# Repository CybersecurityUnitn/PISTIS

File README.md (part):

# PISTIS
### Trusted Computing Architecture for Low-end Embedded Systems 
This repository includes all of the source files and helper scripts for **PISTIS**, a Trusted Execution Environment documented in the scientific paper "*PISTIS: Trusted Computing Architecture for Low-end Embedded Systems*" by Michele Grisafi, Mahmoud Ammar, Marco Roveri and Bruno Crispo. The article, presented at the USENIX Security '22 conference, discloses the content of this repository as an open source contribution to the scientific community.

If you have any questions on the content of the repository, feel free to contact the main author at michele.grisafi@unitn.it.

We highly recommend reading the scientific article before diving into this report!

Following, there is a list of instructions and broad guidelines on how to compile, run and test PISTIS. Depending on the board used for this evaluation, on the programming environment and the tools used, the behaviour of this implementation might change. 

**Disclaimer**: *The following is a working proof of concept. There might be bugs and inconsistencies which were not addressed. Furthermore, the code might damage your MCU board, erasing its memory or degrading its hardware. Use it at your own risk, we do not assume any responsibility for the use of this code, or for the damage it can cause.*

## Table of Content
- [PISTIS](#pistis)
   * [Content of this repository](#content-of-this-repository)
- [Introduction](#introduction)
   * [Isolation details](#isolation-details)
      + [Interrupts](#interrupts)
   * [Memory Map](#memory-map)
- [Running PISTIS](#running-pistis)
   * [Pre requisites](#pre-requisites)
   * [Loading PISTIS TCM (with the default untrusted application)](#loading-pistis-tcm-with-the-default-untrusted-application)
   * [Applications updates / Remote deployments](#applications-updates--remote-deployments)
      + [Compiling the update/application ](#compiling-the-updateapplication)
      + [Deploying untrusted update](#deploying-untrusted-update)
   * [LED signals](#led-signals)
   * [(optional) Loading the custom BSL](#optional-loading-the-custom-bsl)
      + [(optional) Loading the key](#optional-loading-the-key)
   * [Library instrumentation](#library-instrumentation)
      + [Optimisations](#optimisations)
      + [Debug and measurements](#debug-and-measurements)
- [APIs Description](#apis-description)
   * [Data Types](#data-types)
   * [Constants](#constants)
   * [Trusted Application APIs](#trusted-application-apis)
      + [Secure Remote Update](#secure-remote-update)
         - [**callReceiveUpdate**](#callreceiveupdate)
      + [Remote Attestation ](#remote-attestation)
         - [**callAttestCode**](#callattestcode)
   * [Private TCM APIs](#private-tcm-apis)
      + [Functions endpoints](#functions-endpoints)
         - [**launchAppCode**](#launchappcode)
         - [**verify_app_inst**](#verify_app_inst)
         - [**verify_app_cfi**](#verify_app_cfi)
         - [**isImmediateSafeValue**](#isimmediatesafevalue)
         - [**getSecureKey**](#getsecurekey)
         - [**setSecureKey**](#setsecurekey)
   * [Public TCM APIs](#public-tcm-apis)
      + [Assembly endpoints](#assembly-endpoints)
         - [**safe_br_fun**](#safe_br_fun)
         - [**safe_bra_fun**](#safe_bra_fun)
         - [**safe_call_fun**](#safe_call_fun)
         - [**safe_calla_fun**](#safe_calla_fun)
         - [**safe_ret_fun**](#safe_ret_fun)
         - [**safe_reta_fun**](#safe_reta_fun)
         - [**safe_reti_fun**](#safe_reti_fun)
         - [**write_mov_fun**](#write_mov_fun)
         - [**write_movx_fun**](#write_movx_fun)
         - [**write_xor_fun**](#write_xor_fun)
         - [**write_xorx_fun**](#write_xorx_fun)
         - [**write_add_fun**](#write_add_fun)
         - [**write_addx_fun**](#write_addx_fun)
         - [**write_addc_fun**](#write_addc_fun)
         - [**write_addcx_fun**](#write_addcx_fun)
         - [**write_dadd_fun**](#write_dadd_fun)
         - [**write_daddx_fun**](#write_daddx_fun)
         - [**write_sub_fun**](#write_sub_fun)
         - [**write_subx_fun**](#write_subx_fun)
         - [**write_subc_fun**](#write_subc_fun)
         - [**write_subcx_fun**](#write_subcx_fun)

## Content of this repository
- `BSL/`: this folder contains the files required for the modification of the BSL.
    - `IAR_BSL_Source/`: folder containing the IAR Workbench BSL project, used for flashing the new BSL into the device.
    - `modifiedFiles/`: folder containing the modified files used for PISTIS custom BSL.
        - `BSL430_Command_Interpreter.c`: file containing the command interpreter code, used to parse the BSL commands received. We are removing some of the functionalities of the BSL from this file to make room for our PISTIS Secure Storage.
        - `BSL430_Low_Level_Init.s43`: BSL interface for the program, containing the Z-area. We added some entries to this area, such as the BSL unlock function. This will be called by the TCM to enable write privileges over the BSL.
        - `lnk_msp430f5438a.ld`: BSL linker file.
    - `loadKey.c`: source file to load a custom cryptographic key onto PISTIS Safe Storage.
- `UpdateApplication/`: this folder contains all of the required files for compiling a single application for PISTIS. Specifically, it should be populated with the source files of the application.
    - `Makefile`: makefile for compiling the application to be deployed. The result is a file `deployable.out` which is ready for deployment.
    - `src/`: this folder should contain all of the source files of the user application to be compiled (both '.c' and '.s' files). 
- `TCM/`: this folder contains the source code of PISTIS TCM. Morevoer, it contains the source files of a user application (untrusted) that can be deployed alongside it without going over remote update.
    - `Makefile`: makefile for compiling both the untrusted application and the core of TCM. The result is the file `deployable.out` which is ready to be deployed on the MCU.
    - `app/`: folder containing all of the files required for the compilation of the untrusted application
        - `src/`: folder containing all of the source files, both '.c' and '.s' of the untrusted application
        - `Makefile.include`: makefile to be included, containing some directives for the compilation of the application by the main Makefile
    - `core/`: folder containing all of the files required for the PISTIS compilation.
        - `src/`: folder containing all of the source files, both '.c' and '.s' of PISTIS.
            - `core.c|.h`: file containing the source code for the main PISTIS functions.
            - `virt_fun.s`: assembly file containing the definitions of the various virtual functions.
            - `protected_isr.s`: assembly file containing the protected Interrupt Service Routines for the secure interrupt management.
            - `secureContextSwitch.c|.h`: source files for the secure context switch operations which allow the backup and restoration of the RAM, or any other hook operation during a safe context switch.
            - `TCMhook.h`: header file needed by the application (needs to be included in the source files with the '#include' directive) in order to call the secure update function. This file get automatically copied to the `app/src/` directory of the application.
        - `ext_modules/`: folder containing the source files of the various extensions. These files are copied in the `core/src/` folder by the makefile if specified.
            - `secureUpdate.c|.h`: source file for the secure update over serial communication.
            - `raHelper.c|.h`: source files for some backup/restore operations performed by the Remote Attestation.
            - `raHelperAsm.s`: assembly files for some backup/restore opearation performed by the Remote Attestation.
            - `remote_attestation/`: folder containing the HACL implementation of remote attestation.
                - `ra.c`: our implementation, leveraging the HACL library, of the remote attestation.
        
        - `Makefile.include`: makefile to be included, containing some directives for the compilation of the TCM by the main Makefile
- `toolchain/`: folder containing all of the scripts required by the makefile and the deployment process
    - `linkerScript.ld`: modified linker scripts containing the directives for the linker when compiling ONLY the application. Used exclusively by the Makefile.
    - `linkerScriptWithCore.ld`: modified linker scripts containing the directives for the linker when compiling both the application and the TCM. Used exclusively by the Makefile.
    - `loadProgram.py`: python script used to load the program onto the MCU via UART interface (serial port), in compliance with the PISTIS secure update protocol.
    - `metadata.py`: python script in charge of adding the required metadata to the output file. Used exclusively by the Makefile.
    - `modifier.py`: python script in charge of replacing unsafe instructions. Used exclusively by the Makefile.
    - `postprocessor.py`: python script in charge of rejecting the application in case of unsafe instructions (compile-time). Used exclusively by Makefile.
    - `gccLibraries/`: contains all of the statically linked libraries used by GCC and adapted to our toolchain (insertion of NOP slides and reserved registers). The `*.small` files inside refer to libraries using ret and call instead of reta and calla.
        - `libcrt.a`: statically linked library of gcc, compiled from the gcc source folder with the instrumented file `newlib/libgloss/msp430/crt0.S|crt_bss.S` which generates the compiled file `msp430-elf/large/full-memory-range/libgloss/msp430/libcrt.a`. The new file must be placed in `compilerGCCRoot/msp430-elf/lib/large/full-memory-range`. **crt0_movedata** and **crt0_init_bss** have been instrumented (adding the NOP slides). Others, such as call_main and call_exit are not but we should not need them.
        - `libgcc.a`: statically linked library compiled with a modified makefile (to prevent use of reserved registers '*-ffixed-r4 -ffixed-r5 -ffixed-r6*') `sourceGCC/gcc/libgcc/Makefile.in` yielding the file `build/gcc/msp430-elf/large/full-memory-range/libgcc/libgcc.a` to be placed in `compilerGCCRoot/lib/gcc/msp430-elf/9.2.0/large/full-memory-range`
        - `libnosys.a` and `libsim.a`: statically compiled files obtained from the modified makefile (to prevent use of reserved registers '*-ffixed-r4 -ffixed-r5 -ffixed-r6*') `sourceGCC/newlib/libgloss/msp430/Makefile.ini` yielding the files `build/gcc/msp430-elf/large/full-range-memory/libgloss/msp430/libnosys.a|libsim.a`. To be placed in `compiler//msp430-elf/lib/large/full-memory-range`
        - `libc.a`: statically linked library compiled with a modified makefiles (to prevent use of reserved registers '*-ffixed-r4 -ffixed-r5 -ffixed-r6*') `sourceGCC/newlib/newlib/libc/string/Makefile.in`,`sourceGCC/newlib/newlib/libc/string/Makefile.in`,`sourceGCC/newlib/newlib/libc/string/Makefile.in`  yielding the file `build/gcc/msp430-elf/large/full-memopry-range/newlib/libc.a`. 
        The new file must be placed in `compiler/msp430-elf/lib/large/full-memory-range`
    - `helperScripts/`: contains all of the scripts that are helpful in the creation of a proper application image
        - `auxGccPaser.py`: python script that parses a portion of mspdump code and performs the following operations:
            - Format the files to assembly standard.
            - Locates the relevant functions and labels, renaming them so that they can be compiled.
            - Replaces all of the jumps offsets, branches arguments and calla destinations with the correct label so that they can be relocated.
        - `getSizeData.py`: compiles every single test application and retrieves the size info of the various files.
        - `objToHex.py`: python script that parses an object file - created by the `metadata.py` script with the 'debugFiles' set to true - and outputs its content byte by byte so that it can be used in an `injectData.c` source file.
        - `runTimeEvaluation.c`: small C file containing the code used for the runTime evaluation. 
        - `powerConsumption/`: contains all of the scripts for getting the battery consumption with its graphs.
            - `Battery.java`: simulates the battery consumption at various execution rates.
            - `getConsumptions.sh`: script to get all of the power measures via the java script.
            - `getGraph.py`: script to generate graphs for the power measures obtained with the above script.
        - `remote_attestation/verifier/verifier.py`: python script acting simulating a verifier for the Remote Attestation. This script computes the HMAC of a block of data.     
    - `compiler/`: contains the various compilers used by PISTIS, with some compilation libraries and some backups.
        - `include_gcc/`: contains some of the includes files required by the compiler and provided by TI.
        - `msp430-gcc-9.2.0.50_linux64/`: contains the compiled GCC compiler used by PISTIS.
        - `msp430-gcc-9.2.0.50_linux64_backup/`: contains the backup of some of the files modified by our toolchain. These are required for the compilation of uninstrumented applications.
        - `msp430-gcc-9.2.0.50-source-full.tar.gz`: archive containing the modified source files (as described in the `gccLibraries/` folder) for the compilation of the desired libraries and executables.
- `TestApps/`: folder containing all of the test applications used during the evaluation of the proposed PISTIS implementation.
    - `ar-full/`: instrumented and correctly working
    - `bitcount/`: instrumented and correctly working
    - `SHA-256/`: instrumented and correctly working
    - `CopyCodeDMA/`: instrumented and correctly working. The Application copies the content of the flash into RAM with memcpy and with the DMA. In both cases, it checks whether the result is correct. The DMA triggers an interrupt when finished.
    - `CantorSet/`: instrumented and correctly working
    - `PolynomialAddiction/`: instrumented and correctly working
    - `CryptoCode/`: instrumented and correctly working
    - `Serial/`: instrumented and correctly working
    - `CartesianToPolar/`: instrumented and correctly working
    - `LargeSubsequence/`: instrumented and correctly working
    - `PrimeFactorisation/`: instrumented and correctly working
    - `SudokuSolver/`: LINKER problem
    - `TiBenchmark/`: folder containing all of the benchmark applications used by TI and during the evalution of the proposed PISTIS implementation.
        - `whet/`: instrumented and correctly working.
        - `matrixMultiplication/`: instrumented and correctly working.
        - `floatingPointMath/`: instrumented and correctly working.
        - `firFilter/`: instrumented and correctly working.
        - `dhry/`: instrumented and correctly working. NOT WORKING IN CCS
        - `8bitSwitchCase/`: instrumented and correctly working.
        - `16bitSwitchCase/`: instrumented and correctly working.
        - `8bitMath/`: instrumented and correctly working.
        - `16bitMath/`: instrumented and correctly working.
        - `32bitMath/`: instrumented and correctly working.
        - `8bit2dimMatrix/`: instrumented and correctly working.
        - `16bit2dimMatrix/`: instrumented and correctly working.

# Introduction
Pistis is a bare-metal Trusted Execution Environment (TEE) for low-end embedded systems with no support to MMU/MPU. As a TEE, Pistis creates a new execution environments where secure software can run without interference from the untrusted software. We refer to these two environments as the TEE and the Unstrusted Environment (UE). These two environments coexist on the device and are separated by Pistis' software-based primitives, which ensure that the TEE is completely isolated from the UE. 
Being a software-based TEE, Pistis relies on a Trusted Computing Module (TCM) to enforce the isolation between the two environments. The TCM is a piece of software acting as Root of Trust (RoT) that is run in the TEE, alongside other Trusted Applications (TAs). 
These TAs can be deployed by security developers to implement some arbitrary security services. These services can then be leveraged by any software running on the UE using a set of registered APIs. 

## Isolation details
The TCM enforces a software-based separation on the memory and the pheripherals of the device. Similarly to a TrustZone-enabled environment, the TEE has complete control over the entire device, while the UE has only *limited* control over the UE-assigned resources. At boot, the control is given to the TEE, where the TCM performs an initialisation of the device and of the UE environment, afterwhich the control is given to the UE. From that moment onward, there is a master-slave relationship between the TEE and the UE, with the former that is executed only upon request of the UE. 
The UE supports up to one single application binary, which must include the so called Untrusted Application. This application must comply with the Pistis' security policy, which is enforced by the TCM. For instance, the UE is not allowed to access any resource outside of the ones assigned to it by the TCM. Any violation of these policy will be detected at deployment time or at run time, and it trigger a device reset.
Pistis offers a custom toolchain to the UE developers that transparently makes the application binary compliant with Pistis security policy.

### Interrupts
Interrupts are not shared among the UE and the TEE. Conceptually, the TEE has full control over the interrupts, and allows the UE to register its own interrupt handlers. When an interrupt is triggered, the TEE will look up the interrupt table and invoke the right handler. This handler will then be executed in the TEE, which will then return the control to the UE. It is up to the TEE to decide whether to allow the UE to register a handler for a given interrupt or not.

## Memory Map
The software-based isolation of Flash, RAM and MMIO is achieved by means of a custom memory map. The memory map is defined in the linker script and is shown in the following table.

|Address|Name|Description|
|------|-----|-----------|
|0x000-fff|MMIO|Registers for pheripherals|
|0x1000-17ff|BSL/TEE Safe Storage| BSL and PISTIS Secure Storage|
|0x1800-19ff|Information Memory|Hardware info used for calibration of the board|
|0x1c00-2aff|TEE Ram|Ram used by PISTIS Trusted Applications|
|0x2c00-43ff|App RAM|Ram used by the untrusted application |
|0x4400-c3ff|App Code|Where the untrusted yet verified code of the application resides|
|0xc400-f7ff|TEE code|Code of the TEE|
|0xf800-fbff|TEE Secure ISRs|Trampoline for App ISRs. Each entry will load the right App ISR pointer|
|0xfc00-ff7f|TEE virtual functions|Functions invoked by the untrusted app in replacement of the original unsafe instructions|
|0xff80-ffff|TEE ISRs trampoline|Trampoline for TEE ISRs. Interrupts will trigger a lookup of this table, which will lead to the TEE Secure ISRs entries.|
|0x10000-101ff| TEE backup data|Where the PC and status register are saved during interrupts |
|0x10200-103ff| TAs backup data|Where the CPU context (i.e. the registers) are saved during interrupts of TAs|
|0x10400-105ff| App ISRs | Where the app stores the pointers to the ISRs. Each entry stores the address of the APP ISR|
|0x10600-143ff|TEE code|Code of the TEE|
|0x14400-1c3ff|App RoData| Read Only data for the application|
|0x1c400-243ff|Reserved|Used for incoming data|

# Running PISTIS
## Pre requisites
- **linux**: build-essential python3 pip3
- **pip3**: pyserial [matplotlib] [pandas]
- MSP430F5529 board with USB cable (we use a MSP-EXP430F5529LP)
- Code Composer Studio with MSP430 libraries [official link](https://www.ti.com/tool/CCSTUDIO)
- (optional) MSP430 debugger (e.g. MSP430F5529Launchpad version) [board link](https://www.ti.com/tool/MSP-EXP430F5529LP)
- (optional) IAR workbench msp430 Kickstart edition [official link](https://www.iar.com/products/architectures/iar-embedded-workbench-for-msp430/#containerblock_3096)
- (optional) Java for the execution of powerConsumption measurement scripts.

## Loading PISTIS TCM (with the default untrusted application)
In order to secure the microcontroller, the TCM (i.e. the root of trust for our architecture) needs to be loaded before any other program. The folder `TCM/` contains all of the required files for the compilation of PISTIS TCM. Although it is possible to also load an untrusted application right away, to be loaded with the TCM, currently the toolchain does not fully support it. The first initialisation should be perfomed with the default application. 
The following steps must be performed:
- (optional) Copy all of the required untrusted application's source files inside the `TCM/app/src/` folder. The default application only calls the *receiveUpdate()* function from the TCMHooks to initiate a secure update. If such function is not required, or the secureupdate module is not loaded, it should be changed. If no application is loaded, the default one will be. This will initiate a secure update and thus wait for any deployable on the UART communication.
- (optional) Modify the `TCM/Makefile` file to update the binaries paths. By default the toolchain will use the self-contained compiler in this repository.
- Generate the secure deployable image of the TCM using the `make` command from inside the `TCM/` folder. This will generate a `deployable.out` binary (if curious, you can check it with *readelf* to see how it is structured).
- Load the `TCM/deployable.out` image on the device, e.g. using Code Composer Studio 'load' function. If everything was loaded correctly, you should see the following:
    1. The red LED blinks 10 times
    2. The red LED turns on for verification (a few seconds)
    3. The green LED turns on --> ready for incoming updates
- You can also reset the board to start the verification from the beginning.
If you see any other combination of LED check section "LED Signals" for debugging.

## Applications updates / Remote deployments
### Compiling the update/application 
In order to securely deploy an application via PISTIS, a properly crafted update must be compiled. To automate this process, PISTIS offers the folder `UpdateApplication/` which contains the Makefile that must be used. Precisely, the following steps are required to compile the untrusted update:
- Copy all of the source files of the application ('*.c' and '*.s') to the `UpdateApplication/src/` folder. If the folder does not exist it should be created. These are the files that will be compiled.
- Execute the `make` command. This will generate the first executable `deployable.out`. 
- Execute the `make libraries` command to generate some helper files for the instrumentation of the standard library code (check section "Library instrumentation" for more details).
- Execute the `make clean && make` command to generate the final executable `deployable.out` containing the instrumented code for both the application and the standard libraries used by it. NB: this executable is not an ELF file because it contains extra metadata added for PISTIS. To check the original ELF file you can inspect `appWithoutMetadata.out`.
- Proceed with the deployment

### Deploying untrusted update
An application update can only be performed if the MCU is in the receiving update state (see Section **LED signals**). In order to enter this state, the running program must call the `callReceiveUpdate()` function from the `TCMhook.h` header file (as is the case when loading the TCM with the default application). When the MCU is ready to receive the update execute the `/toolchain/loadProgram.py` python script, passing as arguments the final application binary (e.g. `deployable.out`) and the serial port name (e.g. `/dev/ttsyAC2` on Linux or `COM4` on Windows). NB: The serial port might change across executions or systems, please check the serial ports available on your system (especially those that become available as soon as the MCU board is plugged through the USB port).

If the serial port is correct, the script will start uploading the various chunks of the application, waiting for some acknowledgments. As soon as the upload is finished, the script will output a *File sent* to the terminal and the TCM will begin its deployment operations.
As soon as the TCM receives the image it will verify it. If the image is verified with success and the binary does not contain unsafe code (as should be the case if properly compiled using PISTIS toolchain), then it should be lunched by the TCM. Otherwise, the TCM will restart the update process and wait for another valid image. 

Be aware that the code in this repository is compatible with the MSP430 family of microcontroller. However, the code, along with some of the toolchain components, needs to be updated to work with anything different than an MSP430f5529 MCU.

## LED signals
The following table shows the current PISTIS' usage of the various LEDs.

| Green LED | Red LED | Description |
| --------- | ------- | ----------- |
|   blink*10 → ON      | OFF     | The TCM is waiting for an income update       |    
|   ON      | ON      | *reserved*       |
|   OFF     | OFF     | Application started       |
|   OFF     | ON      | Verification of code in progress       |
|   OFF     | blink*10 → ON     | MCU has been reset, starting secure boot       |

## (optional) Loading the custom BSL
Some functionalities of PISTIS are only available if we modify the BSL section of the FLASH. Specifically, we want to reduce some of its codebase in order to make room for the sensitive data. Moreover, we want to modify its interface (z-area) to allow the TCM to interact with it without restrictions. 
To modify the bootloader we need to use IAR workbench msp430, which is a closed-source IDE. Fortunately, we can use its free kickstart edition to modify part of the BSL to support our TCM safe Storage segment. 
The following steps must be be permed:
- Make a copy of the project `BSL/IAR_BSL_Source/IAR_v5_MSP430F552x_USB/` folder.
- Open the local copy with IAR workbench.
- Copy the files in the `BSL/modifiedFiles/` folder to the local copy of the project (these should be placed in the various subdirectories). 
- Compile the project and upload it to the MCU. 
After compiling and uploading the BSL, the MSP430 board will be equipped with the PISTIS Safe Storage segment.

### (optional) Loading the key
Before loading the TCM, we need to load a cryptographic key on the device so that it can be used by the various Trusted Applications (TAs). Note that this step is optional: a cryptographic key is only needed by some specific TAs, e.g. Remote Attestation. Still, the TCM offers some security guarantees which are independent of the PISTIS Safe Storage.
In order to load the key, we can use the `BSL/loadKey.c` application by flashing it on the device, e.g. via CCS Studio. This application will take care of unlocking the BSL and storing a pre-defined key (which can be modified in the source file) on it, locking the BSL afterwards.

## Library instrumentation
Applications using common libc functions, such as *memset*, *memcpy* and similar, need a few extra steps in order to correctly work. Since our untrusted toolchain (i.e. the prepocessor and modifier scripts) only works with source files, it cannot be used to instrument the statically linked binaries. Such binary code derives from statically linked libraries, e.g. the libc library, for instance whenever functions such as *malloc* are required. The binary code is therefore appended to the rest of the instrumented application binary whenever compiling with the GCC linker. The instrumentation of the binary code is automatically performed by our toolchain (althogh it might not be optimal in some cases).

In order to fully optimise the library code used by an application, the following steps should be performed, some of which are manual.
First, our modified linker script assigns the explicit application binary code (i.e. only the binary code derived from the files in `UpdateApplication/src/`, without the libc libraries) to the **.appText** code section. Code sections allow the code to be organised in the binary, allowing the linker to place them in the different parts of the memory. Although our custom .appText section is placed alongside the rest of the application code, which by default would be assigned to the **.text** section, this separation allows us to easily spot the statically linked code. More precisely, while **.appText** will contain our source code, **.text** and **.lower.text** will only contain the code of the libraries. We can therefore fetch it by extracting only the **.text** and the **.lower.text** sections from the assembly dump of the binary file. These sections will indeed only contain the code not derived from our source files, i.e. the statically linked binary code. 

To facilitate this process, we propose an auxiliary script **auxGccParser** that extracts the library code from the deployable and performs some optimisations. This will create the new file `UpdateApplication/src/helper.s` containing the **uninstrumented** code. 

### Optimisations
On top of creating a new assembly file, the **auxGccParser** script will output to console some possible optimisations, e.g. "Possible optimisation with calla r7 found". These are dynamic calls found in the binary code that could be replaced with some static calls, thus improving the performance of the code. With the current toolchain, such optimisations are mere suggestions that require manual verification and inspection. Beware that  some of them could not be valid! To figure out which are indeed valid and apply them, a manual inspection is required. Specifically, the following steps should/could be performed. Examining the newly created file `UpdateApplication/src/helper.s`, for each optimisation mentioned by the output of the above script, do the following:
- Find the dynamic call in question, e.g. `calla r7`, by searching the file.
- Look for the instruction that assign a value to the concerning register (e.g. `mova	#_sbrk_r,	r7`, which loads the address of `_sbrk_r` into `r7`). **NB:** this instruction must be looked for among the assembly instructions **preceding** the dynamic call.
- Replace the dynamic call (e.g. `calla r7`) with a call to the label used in the definition (e.g. `calla #_sbrk_r`).
- Remove the assignation (e.g. `mova	#_sbrk_r,	r7`) since no longer needed.

Note that it might not be trivial deciding whether the optimisation is valid or not: some might seem valid but might instead break the application. As a rule of thumb, the optimisation is valid as long as there is no other register assignation (e.g. for `r7`) between the dynamic call and the spotted assignation. This means that the call will indeed be only to that static address (e.g. `_sbrk_r`). 
**NB**: be aware of the jumps that might make the analysis of the code non-linear.

### Debug and measurements
In order to debug PISTIS or to run measurements, it might be useful to run PISTIS in Code Composer Studio (CCS). To facilitate this, the archive `debugCCSProject.zip` contains an exported CCS project. This can be imported in CCS and used to debug the various components of PISTIS.
Measurements can be computed using the internal clocks as well in debug mode, or with a logical analyser for a more accurate evaluation.

# APIs Description
PISTIS is a TEE composed of three different interfaces: the Trusted Applications APIs, the Private TCM APIs and the Public TCM APIs. The Trusted Applications APIs are endpoints offered by the various Trusted Applications deployed on Pistis. The Private TCM APIs are only exposed to Trusted Applications while the Public TCM APIs can be invoked by the Untrusted Application.

## Data Types
PISTIS uses custom defined data types (_some of these might also be defined by the standard lib_). These are accessible by the Trusted Applications, with the Untrusted Application having to rely on their own data types.

| **Type** | **Description**                      |
|--------------|----------------------------------|
| `uint8_t`      | Unsigned 8-bit integer |
| `int8_t`      | Signed 8-bit integer |
| `uint16_t`      | Unsigned 16-bit integer |
| `int16_t`      | Signed 16-bit integer |
| `uint32_t`      | Unsigned 32-bit integer |
| `int32_t`      | Signed 32-bit integer |
| `bool`      | Boolean type that is unsigned integer of max 255 |
| `char`      | Character type |

## Constants
PISTIS uses several constants that are accessible to its Trusted Applications. These are mostly used to hold the addresses of the memory map that is implemented. *These constants might change with different implementations on different MSP430 devices.*

| **Label** | **Value**  | **Description** |
|--------------|-----------------|-----------------|
| `true`      | `1` | True value|
| `false`      | `0` | False value |
| `REJECTED` | `1` | Indicates a rejected outcome of a verification |
| `VERIFIED` | `0` | Indicates a successful outcome of a verification |
| `KEY_SIZE` | `64` | Size of the secure key |
| `appTopRam` | `0x43FF` | Top adress for the unstrusted application RAM |
| `appBottomRam` | `0x2c00` | Bottom adress for the unstrusted application RAM |
| `appTopText` | `0xc3ff` | Top adress for the unstrusted application code section |
| `appBottomText` | `0x4400` | Bottom adress for the unstrusted application code section |
| `appBottomROdata` | `0x00014400` | Bottom adress for the unstrusted application Read-Only data section |
| `appTopROdata` | `0x0001c3ff` | Top adress for the unstrusted application Read-Only data section |
| `elfAddress` | `0x0001c400` | Address in which the ELF file should be stored during an remote update procedure |
| `bslTop` | `0x17ff` | Top address of the BSL section |
| `bslBottom` | `0x1000` | Bottom address of the BSL section |
| `flashTop` | `0x000243ff` | Top address of the Flash memory |
| `ramTop` | `0x43ff` | Top address of the RAM memory |
| `vectorTop` | `0x0001047c` | Top address of the IVT table in Flash memory |
| `vectorBottom` | `0x00010400` | Bottom address of the IVT table in Flash memory |

## Trusted Application APIs
Pistis comes with two Trusted Applications (TAs): *Secure Remote Update* and *Remote Attestation*. However, PISTIS supports the creation of custom TAs to boost the security guarantee of the system. Each TA can implement one or more security services, which are exposed to the Untrusted Application via a set of APIs. Furthermore, a TA can also call another TA service by using the same endpoints. Following is a list of the currently implemented APIs belonging to our two TAs.

### Secure Remote Update
Trusted Application that updates the entire application binary for the untrusted application. This can be requested by either the TCM or by the application itself. 

#### **callReceiveUpdate**
```c
void callReceiveUpdate();
```

**Description**
Initiate a secure remote update to update the entire untrusted application binary. Once called, this function will blink the green as soon as it is ready to receive the update.
This function does not have any return value because it will completely replace the application binary, thus the return value would not be consumed.

### Remote Attestation 
Trusted Application that attest the entire untrusted application code section. This can be requested by either the TCM or by the application itself. 

#### **callAttestCode**
```c
void callAttestCode(uint8_t * mac, uint8_t * nonce);
```

**Description**
Initiate a remote attestation procedure for the untrusted application code.

**Parameters**
- `uint8_t * mac`: pointer to a 64 bytes long buffer where the MAC will be stored.
- `uint8_t * nonce`: pointer to a 64 bytes long buffer containing the nonce to be used in the MAC computation.

## Private TCM APIs
On top of exposing some APIs to the untrusted domain, PISTIS also has a set of APIs that can be used only within Trusted Applications. These are C functions rather than assembly, and allow PISTIS to perform some privileged task on behalf of the TAs.

### Functions endpoints
#### **launchAppCode**
```c
void launchAppCode();
```
**Description**
Locks the memory controller, enables the interrupts and then executes the application code by jumping to the first untrusted application instruction. This function can be called at the end of a successful verification to start the untrusted application. **If this function is called after a unsuccessful verification, i.e. PISTIS detected some unsafe instructions in the untrusted application, it will lead to an unsafe execution with a potential breach of the system security.**

#### **verify_app_inst**
```c
bool verify_app_inst(uint16_t address, uint16_t lastAddress);
```
**Description**
Lunch the instruction verification for a certain untrusted section of code to detect the presece of unsafe instructions. This function can be used by any Trusted Application that wants to make sure that a specific portion of untrusted code is safe to be executed. **It should be called before `verify_app_cfi`.**

**Parameters**
- `uint16_t address`: address from which the verification should start, e.g. the first instruction of the application.
- `uint16_t lastAddress`: address that the verification should reach, after which the verification ends, e.g. the last instruction of the application.

**Return Value**
Upon successful verification and if the code does not contain unsafe instruction, the return value is `VERIFIED`, otherwise it is `REJECTED`.

#### **verify_app_cfi**
```c
bool verify_app_cfi(uint16_t address, uint16_t lastAddress);
```
**Description**
Lunch the instruction verification for a certain untrusted section of code to detect violation of the control flow. This function can be used by any Trusted Application that wants to make sure that a specific portion of untrusted code is safe to be executed. **It should be called after with `verify_app_`. It does not validate the control flow of the application (whether the application will function correctly), but rather if the control flow of the application can violate the security of the system.**

**Parameters**
- `uint16_t address`: address from which the verification should start, e.g. the first instruction of the application.
- `uint16_t lastAddress`: address that the verification should reach, after which the verification ends, e.g. the last instruction of the application.

**Return Value**
Upon successful verification and if the code does not contain unsafe instruction, the return value is `VERIFIED`, otherwise it is `REJECTED`.

#### **isImmediateSafeValue**
```c
bool isImmediateSafeValue(uint32_t destination);
```
**Description**
Check whether a certain address is safe to be called from the untrusted code. This will perform several checks, mainly comparing the given address with the memory boundaries and with the various public TCM APIs.

**Parameters**
- `uint32_t destination`: destination address to be checked, where the code should jump to.

**Return Value**
Upon successful verification, the return value is `true`, indicating that it is a static safe value, or `false` indicating that the address is unsafe to jump to.

#### **getSecureKey**
```c
void getSecureKey(uint8_t * key);
```

**Description**
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
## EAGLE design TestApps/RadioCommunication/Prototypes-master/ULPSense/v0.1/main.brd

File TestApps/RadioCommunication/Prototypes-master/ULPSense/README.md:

# Ultra Low-Power Sensing
 [Version 0.1](v0.1)

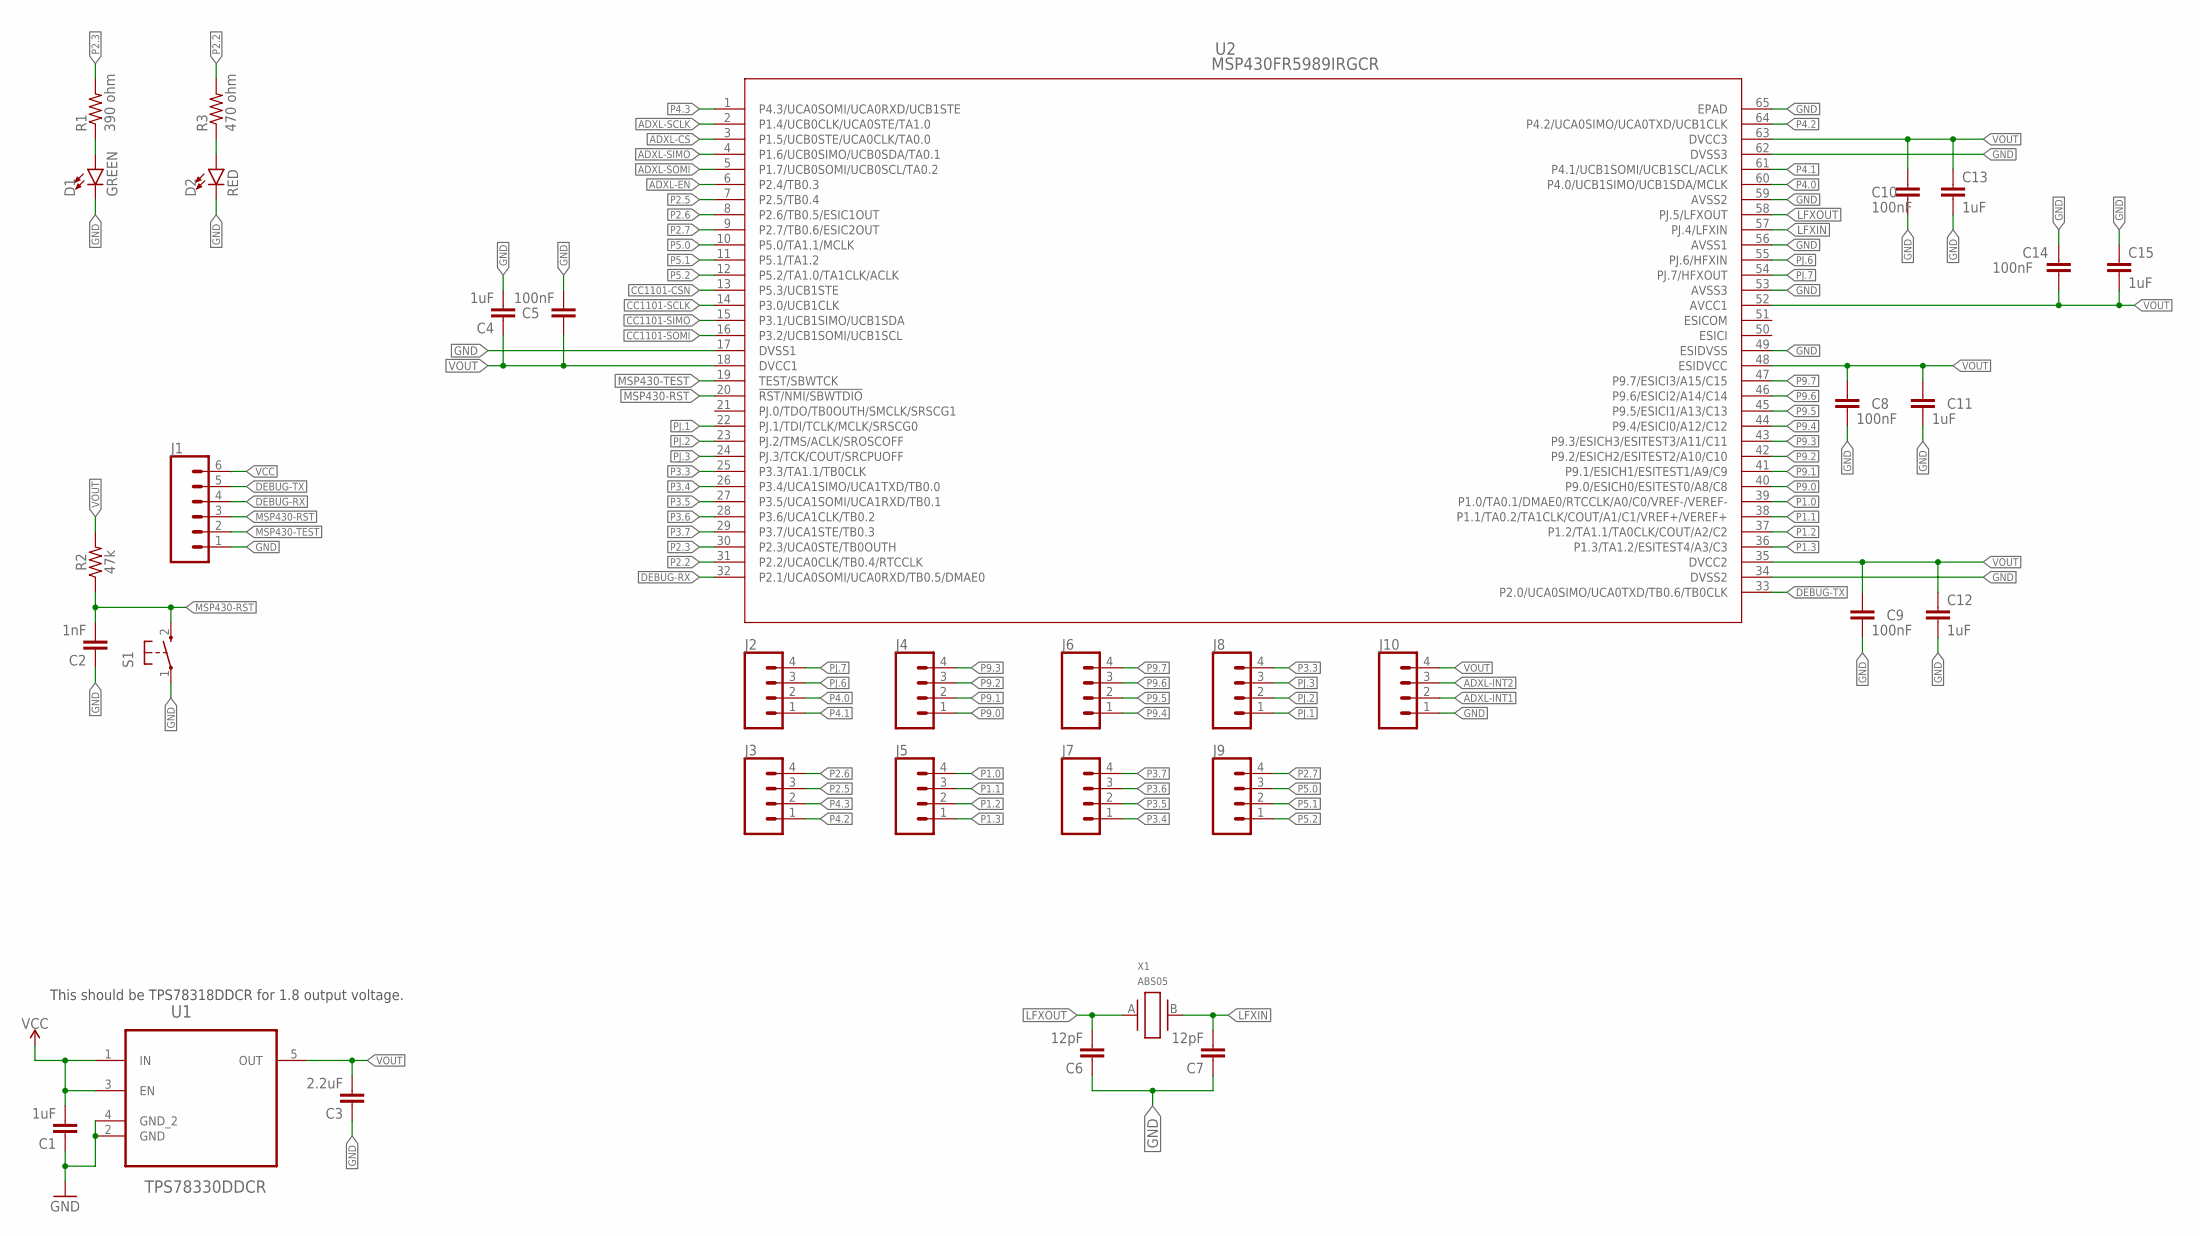
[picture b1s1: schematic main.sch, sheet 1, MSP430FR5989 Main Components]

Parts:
C1, C4, C11, C12, C13, C15: 1uF; 0603
C2: 1nF; 0603
C3: 2.2uF; 0603
C5, C8, C9, C10, C14: 100nF; 0603
C6, C7: 12pF; 0603; MPN CL10C120JB8NNNC
D1: GREEN; LED-0603
D2: RED; LED-0603
J1: CONN_06SILK_FEMALE_PTH; 1X06
J2, J3, J4, J5, J6, J7, J8, J9, J10: CONN_041.27MM; 1X04_1.27MM
R1: 390 ohm; 0402
R2: 47k; 0603
R3: 470 ohm; 0402
S1: ELECTRICALMETER_PB; ELECTRICALMETER_PBTH
U1: TPS78330DDCR; SOT95P280X110-5N
U2: MSP430FR5989IRGCR; RGC64_4P25X4P25
X1: ABS05; MPN ABS05-32.768KHZ-9-T

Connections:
ADXL-CS: U2.3 (P1.5/UCB0STE/UCA0CLK/TA0.0); also elsewhere on the board
ADXL-EN: U2.6 (P2.4/TB0.3); also elsewhere on the board
ADXL-INT1: J10.2; also elsewhere on the board
ADXL-INT2: J10.3; also elsewhere on the board
ADXL-SCLK: U2.2 (P1.4/UCB0CLK/UCA0STE/TA1.0); also elsewhere on the board
ADXL-SIMO: U2.4 (P1.6/UCB0SIMO/UCB0SDA/TA0.1); also elsewhere on the board
ADXL-SOMI: U2.5 (P1.7/UCB0SOMI/UCB0SCL/TA0.2); also elsewhere on the board
CC1101-CSN: U2.13 (P5.3/UCB1STE); also elsewhere on the board
CC1101-SCLK: U2.14 (P3.0/UCB1CLK); also elsewhere on the board
CC1101-SIMO: U2.15 (P3.1/UCB1SIMO/UCB1SDA); also elsewhere on the board
CC1101-SOMI: U2.16 (P3.2/UCB1SOMI/UCB1SCL); also elsewhere on the board
DEBUG-RX: J1.4, U2.32 (P2.1/UCA0SOMI/UCA0RXD/TB0.5/DMAE0)
DEBUG-TX: J1.5, U2.33 (P2.0/UCA0SIMO/UCA0TXD/TB0.6/TB0CLK)
GND: C1.1, C2.1, C3.1, C4.2, C5.2, C6.1, C7.1, C8.2, C9.2, C10.2, C11.2, C12.2, C13.2, C14.1, C15.1, D1.C, D2.C, J1.1, J10.1, S1.1, U1.2 (GND), U1.4 (GND_2), U2.17 (DVSS1), U2.34 (DVSS2), U2.49 (ESIDVSS), U2.53 (AVSS3), U2.56 (AVSS1), U2.59 (AVSS2), U2.62 (DVSS3), U2.65 (EPAD); also elsewhere on the board
LFXIN: C7.2, U2.57 (PJ.4/LFXIN), X1.B (2)
LFXOUT: C6.2, U2.58 (PJ.5/LFXOUT), X1.A (1)
MSP430-RST: C2.2, J1.3, R2.1, S1.2 (S), U2.20 (!RST/NMI/SBWTDIO)
MSP430-TEST: J1.2, U2.19 (TEST/SBWTCK)
unnamed: D1.A, R1.1
unnamed: D2.A, R3.1
P1.0: J5.4, U2.39 (P1.0/TA0.1/DMAE0/RTCCLK/A0/C0/VREF-/VER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)
P1.1: J5.3, U2.38 (P1.1/TA0.2/TA1CLK/COUT/A1/C1/VREF+/VERE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)
P1.2: J5.2, U2.37 (P1.2/TA1.1/TA0CLK/COUT/A2/C2)
P1.3: J5.1, U2.36 (P1.3/TA1.2/ESITEST4/A3/C3)
P2.2: R3.2, U2.31 (P2.2/UCA0CLK/TB0.4/RTCCLK)
P2.3: R1.2, U2.30 (P2.3/UCA0STE/TB0OUTH)
P2.5: J3.3, U2.7 (P2.5/TB0.4)
P2.6: J3.4, U2.8 (P2.6/TB0.5/ESIC1OUT)
P2.7: J9.4, U2.9 (P2.7/TB0.6/ESIC2OUT)
P3.3: J8.4, U2.25 (P3.3/TA1.1/TB0CLK)
P3.4: J7.1, U2.26 (P3.4/UCA1SIMO/UCA1TXD/TB0.0)
P3.5: J7.2, U2.27 (P3.5/UCA1SOMI/UCA1RXD/TB0.1)
P3.6: J7.3, U2.28 (P3.6/UCA1CLK/TB0.2)
P3.7: J7.4, U2.29 (P3.7/UCA1STE/TB0.3)
P4.0: J2.2, U2.60 (P4.0/UCB1SIMO/UCB1SDA/MCLK)
P4.1: J2.1, U2.61 (P4.1/UCB1SOMI/UCB1SCL/ACLK)
P4.2: J3.1, U2.64 (P4.2/UCA0SIMO/UCA0TXD/UCB1CLK)
P4.3: J3.2, U2.1 (P4.3/UCA0SOMI/UCA0RXD/UCB1STE)
P5.0: J9.3, U2.10 (P5.0/TA1.1/MCLK)
P5.1: J9.2, U2.11 (P5.1/TA1.2)
P5.2: J9.1, U2.12 (P5.2/TA1.0/TA1CLK/ACLK)
P9.0: J4.1, U2.40 (P9.0/ESICH0/ESITEST0/A8/C8)
P9.1: J4.2, U2.41 (P9.1/ESICH1/ESITEST1/A9/C9)
P9.2: J4.3, U2.42 (P9.2/ESICH2/ESITEST2/A10/C10)
P9.3: J4.4, U2.43 (P9.3/ESICH3/ESITEST3/A11/C11)
P9.4: J6.1, U2.44 (P9.4/ESICI0/A12/C12)
P9.5: J6.2, U2.45 (P9.5/ESICI1/A13/C13)
P9.6: J6.3, U2.46 (P9.6/ESICI2/A14/C14)
P9.7: J6.4, U2.47 (P9.7/ESICI3/A15/C15)
PJ.1: J8.1, U2.22 (PJ.1/TDI/TCLK/MCLK/SRSCG0)
PJ.2: J8.2, U2.23 (PJ.2/TMS/ACLK/SROSCOFF)
PJ.3: J8.3, U2.24 (PJ.3/TCK/COUT/SRCPUOFF)
PJ.6: J2.3, U2.55 (PJ.6/HFXIN)
PJ.7: J2.4, U2.54 (PJ.7/HFXOUT)
VCC: C1.2, J1.6, U1.1 (IN), U1.3 (EN)
VOUT: C3.2, C4.1, C5.1, C8.1, C9.1, C10.1, C11.1, C12.1, C13.1, C14.2, C15.2, J10.4, R2.2, U1.5 (OUT), U2.18 (DVCC1), U2.35 (DVCC2), U2.48 (ESIDVCC), U2.52 (AVCC1), U2.63 (DVCC3); also elsewhere on the board

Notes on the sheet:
This should be TPS78318DDCR for 1.8 output voltage.

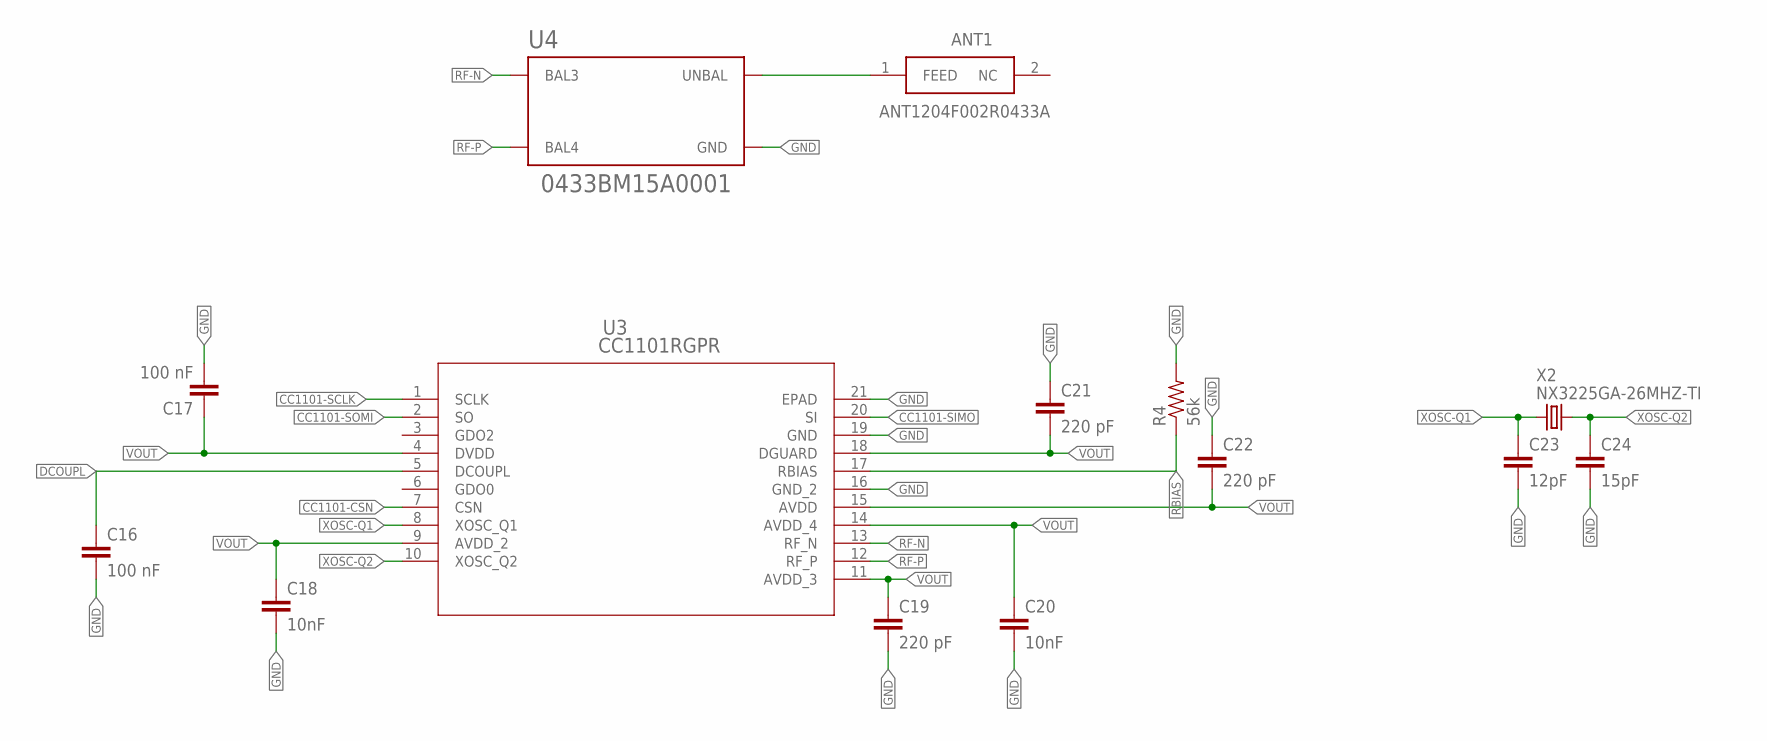
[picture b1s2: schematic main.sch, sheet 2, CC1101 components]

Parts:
ANT1: ANT1204F002R0433A; ANTC12340X180N
C16, C17: 100 nF; 0603; MPN GCJ188R71H104KA12D
C18, C20: 10nF; 0603; MPN GCJ188R71H104KA12D
C19, C21, C22: 220 pF; 0603; MPN GCJ188R71H104KA12D
C23: 12pF; 0603; MPN 06035A120FAT2A
C24: 15pF; 0603; MPN C1608C0G1H150J080AA
R4: 56k; 0603; MPN ERJ-3GEYJ563V
U3: CC1101RGPR; RGP20_2P4X2P4
U4: 0433BM15A0001; XXXXBM15A0001
X2: NX3225GA-26MHZ-TI; XTAL-3.2X2.5

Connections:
CC1101-CSN: U3.7 (CSN); also elsewhere on the board
CC1101-SCLK: U3.1 (SCLK); also elsewhere on the board
CC1101-SIMO: U3.20 (SI); also elsewhere on the board
CC1101-SOMI: U3.2 (SO); also elsewhere on the board
DCOUPL: C16.1, U3.5 (DCOUPL)
GND: C16.2, C17.2, C18.2, C19.2, C20.2, C21.1, C22.1, C23.2, C24.2, R4.2, U3.16 (GND_2), U3.19 (GND), U3.21 (EPAD), U4.2 (GND), U4.5 (GND), U4.6 (GND); also elsewhere on the board
unnamed: ANT1.1 (FEED), U4.1 (UNBAL)
RBIAS: R4.1, U3.17 (RBIAS)
RF-N: U3.13 (RF_N), U4.3 (BAL3)
RF-P: U3.12 (RF_P), U4.4 (BAL4)
VOUT: C17.1, C18.1, C19.1, C20.1, C21.2, C22.2, U3.4 (DVDD), U3.9 (AVDD_2), U3.11 (AVDD_3), U3.14 (AVDD_4), U3.15 (AVDD), U3.18 (DGUARD); also elsewhere on the board
XOSC-Q1: C23.1, U3.8 (XOSC_Q1), X2.1
XOSC-Q2: C24.1, U3.10 (XOSC_Q2), X2.3 (2)

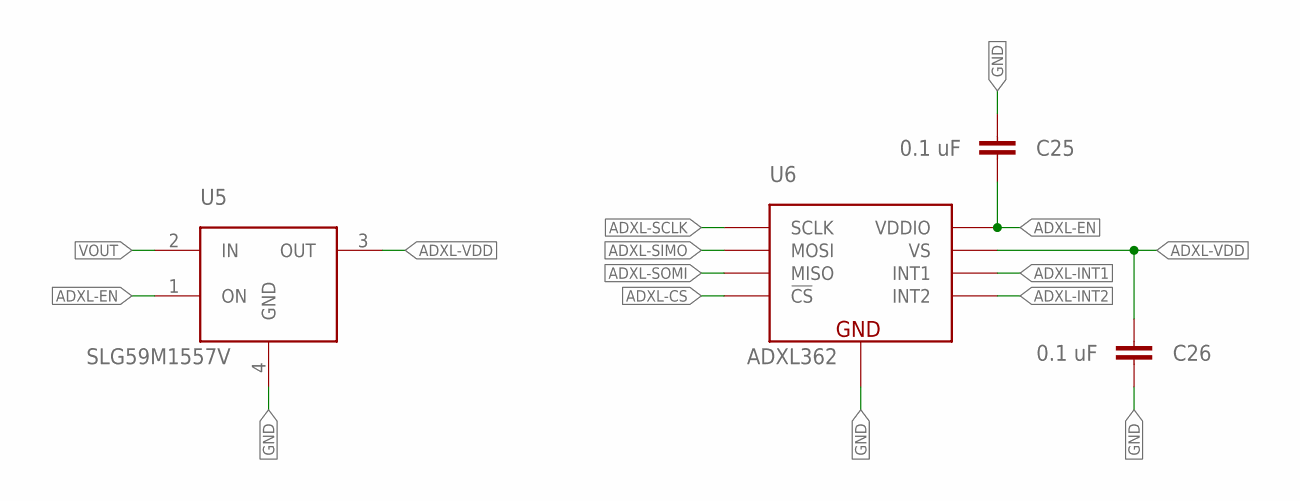
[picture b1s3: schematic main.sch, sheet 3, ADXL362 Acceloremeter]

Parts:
C25, C26: 0.1 uF; 0603
U5: SLG59M1557V; 4STDFN; MPN SLG59M1557V; MOUSER 402-SLG59M1557V
U6: ADXL362; MPN ADXL362BCCZ-RL7; DIGIKEY ADXL362BCCZ-RL7CT-ND

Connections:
ADXL-CS: U6.P$8 (!CS); also elsewhere on the board
ADXL-EN: C25.1, U5.1 (ON), U6.P$1 (VDDIO); also elsewhere on the board
ADXL-INT1: U6.P$11 (INT1); also elsewhere on the board
ADXL-INT2: U6.P$9 (INT2); also elsewhere on the board
ADXL-SCLK: U6.P$4 (SCLK); also elsewhere on the board
ADXL-SIMO: U6.P$6 (MOSI); also elsewhere on the board
ADXL-SOMI: U6.P$7 (MISO); also elsewhere on the board
ADXL-VDD: C26.2, U5.3 (OUT), U6.P$14 (VS)
GND: C25.2, C26.1, U5.4 (GND), U6.P$12 (GND), U6.P$13 (GND), U6.P$16 (GND); also elsewhere on the board
VOUT: U5.2 (IN); also elsewhere on the board

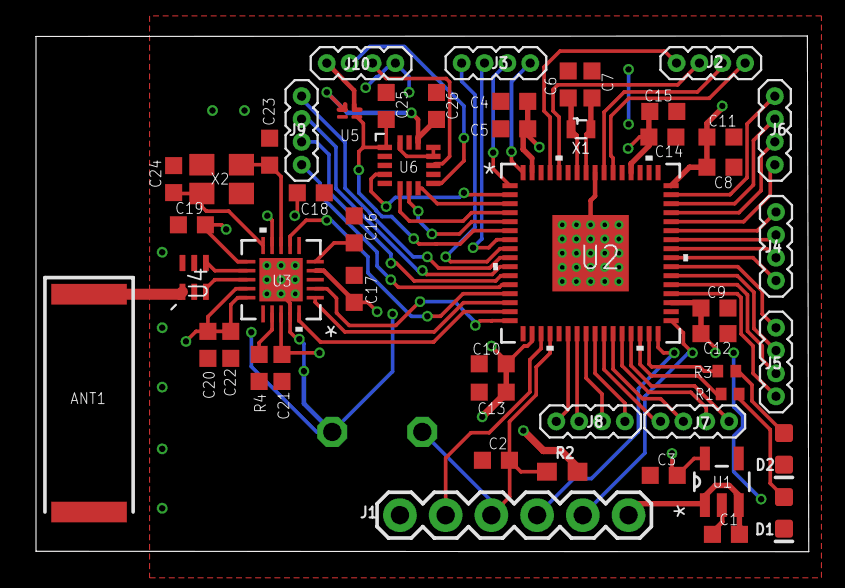
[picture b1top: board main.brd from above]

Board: 2 copper layers, 42.9 x 28.7 mm, 52 parts (0 on the bottom side), 64 nets.

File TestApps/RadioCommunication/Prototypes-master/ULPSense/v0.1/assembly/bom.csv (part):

Qty,Line Item,Manufacturer,MPN,Octopart URL,Schematic Reference,Internal Part Number,Description,Total Qty (@ Batch Size: 1),SKU,SKU,SKU,Packaging,Packaging,Packaging,Unit Price (@ Batch Size: 1),Unit Price (@ Batch Size: 1),Unit Price (@ Batch Size: 1),In Stock,In Stock,In Stock,MOQ,MOQ,MOQ,URL,URL,URL,Distributor [Lowest Price (Overall)],SKU [Lowest Price (Overall)],Packaging [Lowest Price (Overall)],Unit Price (@ Batch Size: 1) [Lowest Price (Overall)],Line Total [Lowest Price (Overall)],Batch Total [Lowest Price (Overall)],In Stock [Lowest Price (Overall)],MOQ [Lowest Price (Overall)],URL [Lowest Price (Overall)],Notes
,,,,,,,,,Digi-Key,Farnell,Mouser,Digi-Key,Farnell,Mouser,Digi-Key,Farnell,Mouser,Digi-Key,Farnell,Mouser,Digi-Key,Farnell,Mouser,Digi-Key,Farnell,Mouser,,,,,,,,,,
1,TPS78318DDCR,Texas Instruments,TPS78318DDCR,https://octopart.com/tps78318ddcr-texas+instruments-21548115,U1,,TI Voltage Regulator 1.8V,1,296-40964-1-ND,,595-TPS78318DDCR,Cut Tape,,Tape & Reel,0.83,,0.92,8587,,3146,1,,1,https://octopart.com/click/track?ai=8237&sig=08aeb25&sid=459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,,https://octopart.com/click/track?ai=8237&sig=08ed5d3&sid=240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,Rochester Electronics,TPS78318DDCR,,0.4,0.4,0.4,2514,1,https://octopart.com/click/track?ai=8237&sig=0ee6881&sid=583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,TI Voltage Regulator 1.8V
1,MSP430FR5989IRGCR,Texas Instruments,MSP430FR5989IRGCR,https://octopart.com/msp430fr5989irgcr-texas+instruments-48723452,U2,,TI msp430fr5989 microcontroller,1,296-51459-1-ND,,,Cut Tape,,,7.16,,,2626,,,1,,,https://octopart.com/click/track?c=1&ai=8237&sig=09ebab2&sid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,,,Texas Instruments,MSP430FR5989IRGCR,Cut Tape,6.4,6.4,6.4,5955,1,https://octopart.com/click/track?ai=8237&sig=0196a65&sid=272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,TI msp430fr5989 microcontroller
1,TPS78330DDCR,Texas Instruments,TPS78330DDCR,https://octopart.com/tps78330ddcr-texas+instruments-14412359,,,TI Voltage Regulator 3.3V,1,296-25880-1-ND,2352487,595-TPS78330DDCR,Cut Tape,,Tape & Reel,0.83,1.0286275297320213,0.91,83012,915,35091,1,1,1,https://octopart.com/click/track?ai=8237&sig=07a4d25&sid=459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,https://octopart.com/click/track?ai=8237&sig=0ba60e6&sid=819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,https://octopart.com/click/track?ai=8237&sig=087dd5c&sid=240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,Rochester Electronics,TPS78330DDCR,,0.4,0.4,0.4,153,1,https://octopart.com/click/track?ai=8237&sig=050705d&sid=583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,TI Voltage Regulator 3.3V
1,311-390LRCT-ND,Yageo,RC0402FR-0739RL,https://octopart.com/rc0402fr-0739rl-yageo-39817195,R1,,"390 Ohms ±1% 0.063W, 1/16W Chip Resistor 0402 (1005 Metric) Moisture Resistant Thick Film",1,311-39.0LRCT-ND,9239065,603-RC0402FR-0739RL,Cut Tape,,Tape & Reel,0.1,,0.1,1998277,58970,145165,1,10,1,https://octopart.com/click/track?ai=8237&sig=0b800c0&sid=459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,https://octopart.com/click/track?ai=8237&sig=02aca5c&sid=819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,https://octopart.com/click/track?ai=8237&sig=0686fe5&sid=240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,Future Electronics,RC0402FR-0739RL-CUTT,Cut Tape,0.0023,0.0023,0.0023,8361,1,https://octopart.com/click/track?ai=8237&sig=08696fd&sid=245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,
1,1276-5102-1-ND,Samsung,RC1608J473CS,https://octopart.com/rc1608j473cs-samsung-86365,R2,,47K resistor,1,1276-5102-1-ND,,,Cut Tape,,,0.1,,,88578,,,1,,,https://octopart.com/click/track?ai=8237&sig=070752c&sid=459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,,,Component Electronics,RC1608J473CS,,0.07692,0.07692,0.07692,250,1,https://octopart.com/click/track?ai=8237&sig=0dc3dfc&sid=172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,47K resistor
1,311-470LRCT-ND,Yageo,RC0402FR-074R7L,https://octopart.com/rc0402fr-074r7l-yageo-40952548,R3,,"470 Ohms ±1% 0.063W, 1/16W Chip Resistor 0402 (1005 Metric) Moisture Resistant Thick Film",1,311-4.70LRCT-ND,1458799,603-RC0402FR-074R7L,Cut Tape,,Tape & Reel,0.1,,0.1,2624662,24410,546045,1,10,1,https://octopart.com/click/track?ai=8237&sig=07651e7&sid=459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,https://octopart.com/click/track?ai=8237&sig=0d2521c&sid=819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,https://octopart.com/click/track?ai=8237&sig=07be493&sid=240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,"Arrow Electronics, Inc.",RC0402FR-074R7L,Cut Tape,0.0942,0.0942,0.0942,8687,1,https://octopart.com/click/track?ai=8237&sig=05e07bc&sid=110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,
1,160-1183-1-ND,Lite-On,LTST-C190GKT,https://octopart.com/ltst-c190gkt-lite-on-549821,D1,,Green 569nm LED Indication - Discrete 2.1V 0603 (1608 Metric),1,160-1183-1-ND,,859-LTST-C190GKT,Cut Tape,,Tape & Reel,0.26,,0.25,759745,,303638,1,,1,https://octopart.com/click/track?ai=8237&sig=0316225&sid=459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,,https://octopart.com/click/track?ai=8237&sig=0d18904&sid=240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,Wuhan P&S,LTST-C190GKT,,0.03,0.03,0.03,20000,1,https://octopart.com/click/track?ai=8237&sig=0ba50ad&sid=149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,
1,160-1181-1-ND,Lite-On,LTST-C190CKT,https://octopart.com/ltst-c190ckt-lite-on-549819,D2,,Red 638nm LED Indication - Discrete 1.8V 0603 (1608 Metric),1,160-1181-1-ND,,859-LTST-C190CKT,Cut Tape,,Tape & Reel,0.31,,0.3,538704,,134365,1,,1,https://octopart.com/click/track?ai=8237&sig=0c1654a&sid=459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,,https://octopart.com/click/track?ai=8237&sig=07248fd&sid=240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,Voyager Components,LTST-C190CKTLITE-ON810,,0.04,0.04,0.04,1684,1,https://octopart.com/click/track?ai=8237&sig=004eac6&sid=242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,
1,CL10B102KB8NNNC,Samsung,CL10B102KB8NNNC,https://octopart.com/cl10b102kb8nnnc-samsung-9301522,C2,,1 nF ceramic capacitor,1,1276-1018-1-ND,3013403,,Cut Tape,,,0.1,,,1706697,7230,,1,10,,https://octopart.com/click/track?ai=8237&sig=0138e6a&sid=459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,https://octopart.com/click/track?ai=8237&sig=0ca5d2b&sid=819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,,"Arrow Electronics, Inc.",CL10B102KB8NNNC,,0.0044,0.0044,0.0044,11425,1,https://octopart.com/click/track?ai=8237&sig=0e1c073&sid=110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,1 nF ceramic capacitor
1,P12216SCT-ND,Panasonic,EVQ-21304M,https://octopart.com/evq-21304m-panasonic-39992935,S1,,Tactile Switch,1,P12216SCT-ND,,,Cut Tape,,,0.22,,,3651,,,1,,,https://octopart.com/click/track?ai=8237&sig=0e3d37e&sid=459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,,,"Arrow Electronics, Inc.",EVQ-21304M,Cut Tape,0.209,0.209,0.209,52,1,https://octopart.com/click/track?ai=8237&sig=0085bab&sid=110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,Tactile Switch
6,1276-1182-1-ND,Samsung,CL10A105KP8NNNC,https://octopart.com/cl10a105kp8nnnc-samsung-19831461,"C1, C4, C11, C12, C13, C15",,1 uF ceramic capacitor,6,1276-1182-1-ND,3013385,,Cut Tape,,,0.1,,,4091857,8910,,1,10,,https://octopart.com/click/track?ai=8237&sig=077d28c&sid=459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,https://octopart.com/click/track?ai=8237&sig=0742962&sid=819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,,Future Electronics,CL10A105KP8NNNC-CUTT,Cut Tape,0.0112,0.0672,0.0672,1290,1,https://octopart.com/click/track?ai=8237&sig=0ee3bdb&sid=245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,1 uF ceramic capacitor
7,732-7939-1-ND,Würth Elektronik,885012206020,https://octopart.com/885012206020-w%C3%BCrth+elektronik-53914729,"C5,  C8, C9, C10, C14, C16, C17",,100 nF ceramic capacitor,7,732-7939-1-ND,2495168,710-885012206020,Cut Tape,,Tape & Reel,0.1,,0.1,53711,13107,50114,1,10,1,https://octopart.com/click/track?ai=8237&sig=0e4d41a&sid=459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,https://octopart.com/click/track?ai=8237&sig=0fa8f3a&sid=819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,https://octopart.com/click/track?ai=8237&sig=07c433c&sid=240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,Newark,75Y6022,Cut Tape,0.017,0.11900000000000001,0.11900000000000001,8000,1,https://octopart.com/click/track?ai=8237&sig=0554afb&sid=240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,100 nF ceramic capacitor
1,535-11897-1-ND,Abracon,ABS05-32.768KHZ-9-T,https://octopart.com/abs05-32.768khz-9-t-abracon-24147054,X1,,12.5 pF 32 KHz external crystal,1,535-11897-1-ND,2467858,815-ABS05-32.768K9T,Cut Tape,,Tape & Reel,0.89,,0.89,174038,1537,7255,1,5,1,https://octopart.com/click/track?ai=8237&sig=052e23f&sid=459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,https://octopart.com/click/track?ai=8237&sig=0fc08db&sid=819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,https://octopart.com/click/track?ai=8237&sig=0858c0a&sid=240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,"Arrow Electronics, Inc.",ABS05-32.768KHZ-9-T,Cut Tape,0.8443,0.8443,0.8443,4549,1,https://octopart.com/click/track?ai=8237&sig=04dad38&sid=110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,12.5 pF 32 KHz external crystal
3,CL10C120JB8NNNC,Samsung,CL10C120JB8NNNC,https://octopart.com/cl10c120jb8nnnc-samsung-9301588,"C6, C7, C23",,12 pF ceramic capacitor,3,1276-1254-1-ND,,,Cut Tape,,,0.1,,,175175,,,1,,,https://octopart.com/click/track?ai=8237&sig=0931c25&sid=459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,,,Future Electronics,CL10C120JB8NNNC-CUTT,Cut Tape,0.0082,0.024600000000000004,0.024600000000000004,281,1,https://octopart.com/click/track?ai=8237&sig=05b571c&sid=245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,12 pF ceramic capacitor
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
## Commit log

2022-07-28 Artifact Evaluation Passed.
2022-08-08 Clean, copyright and license
2023-03-28 Bug fixes to the secureUpdate TA, added circular compilation for external libraries, added some comments.
2023-04-11 Update to the TCMhook so that it uses the static address rather than a label. This allows updates to use the callReceiveUpdate() function without triggering a compilation error (reference not found).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
2023-05-17 1) Fixed a bug where CALLA and RETA where replaced manually with CALL and RET. This, however, messed up the stack calculation. 2) Added the 9.3 compiler for future use 3) Added green blinking led fee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
2023-05-17 Modified the README and added the CCS debug project
2023-10-03 Documentation and refactoring
2024-10-22 Bug fix

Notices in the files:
parts and their libraries:
SparkFun-Connectors: Licensing: Creative Commons ShareAlike 4.0 International - https://creativecommons.org/licenses/by-sa/4.0
